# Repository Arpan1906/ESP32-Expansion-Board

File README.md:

# ESP32 Expansion Board

Designed by **Arpan Mukherjee**  
Date: 03/02/2026  

This repository contains the design files, schematics, and PCB layouts for an **ESP32 Expansion Board**. The board is built to simplify prototyping and interfacing with the ESP32-Devkit, providing organized pin headers, regulated power supply, and easy access to GPIOs.

---

## 📌 Features
- Compatible with **ESP32-Devkit V1**.
- Organized pin headers for:
  - Power: 3V3, 5V, VIN, GND
  - Digital I/O: D1 – D39
  - UART: RX0/TX0, RX2/TX2
  - Special pins: EN, VP, VN
- On-board **7805T voltage regulator** for +12V input → +5V output.
- Decoupling capacitors (C1, C2) for stable power.
- Jumper headers (JP1 – JP4) for flexible interfacing.
- Clear silkscreen labels for easy identification.
- Compact and symmetrical PCB layout for neat prototyping.

---

## Schematic

## Top Layer

## Bottom Layer

## Top Layer (Prior to Fabrication)

## Bottom Layer (Prior to Fabrication)

## 📂 Repository Contents
- **TOP.pdf** → Top layer PCB layout  
- **Bottom.pdf** → Bottom layer PCB layout  
- **Schematics** → ESP32 Expansion Board circuit diagram  
- **PCB Images** → Rendered PCB layouts for visualization  

---

## ⚡ Hardware Overview

### Power Section
- Input: +12V DC  
- Regulator: 7805T → +5V output  
- Outputs: +5V, 3V3, GND available on headers  

### Pin Mapping
| Left Header | Right Header | Center Header |
|-------------|--------------|---------------|
| 3V3, GND, D15, D2, D4, D5, D18, D19, D21, RX0, TX0, D22, D23 | +5V, GND, D13, D12, D14, D27, D26, D25, D33, D32, D35, D34, VN/D39, VP/D36, EN | IO15, IO2, IO4, IO16, IO17, IO5, IO18, IO19, IO21, IO3, IO1, IO22, IO23 |

---

## 🔧 How to Use
1. Connect **ESP32-Devkit V1** to the expansion board.  
2. Provide **+12V input** to the power terminal.  
3. Use headers to interface sensors, modules, or external circuits.  
4. Configure jumpers (JP1–JP4) as needed for custom connections.  

---

## 📸 Visuals
PCB layouts and schematics are included in this repository (`TOP.pdf`, `Bottom.pdf`, and schematic diagrams).  

---

## 📺 Additional Resources
- YouTube Channel: [The ElectroPath](https://www.youtube.com/@The_ElectroPath)  

---

## 📜 License
This project is released under the **MIT License**. You are free to use, modify, and distribute with attribution.

---

## 🙌 Acknowledgments
- Designed and developed by **Arpan Mukherjee (ECE)**

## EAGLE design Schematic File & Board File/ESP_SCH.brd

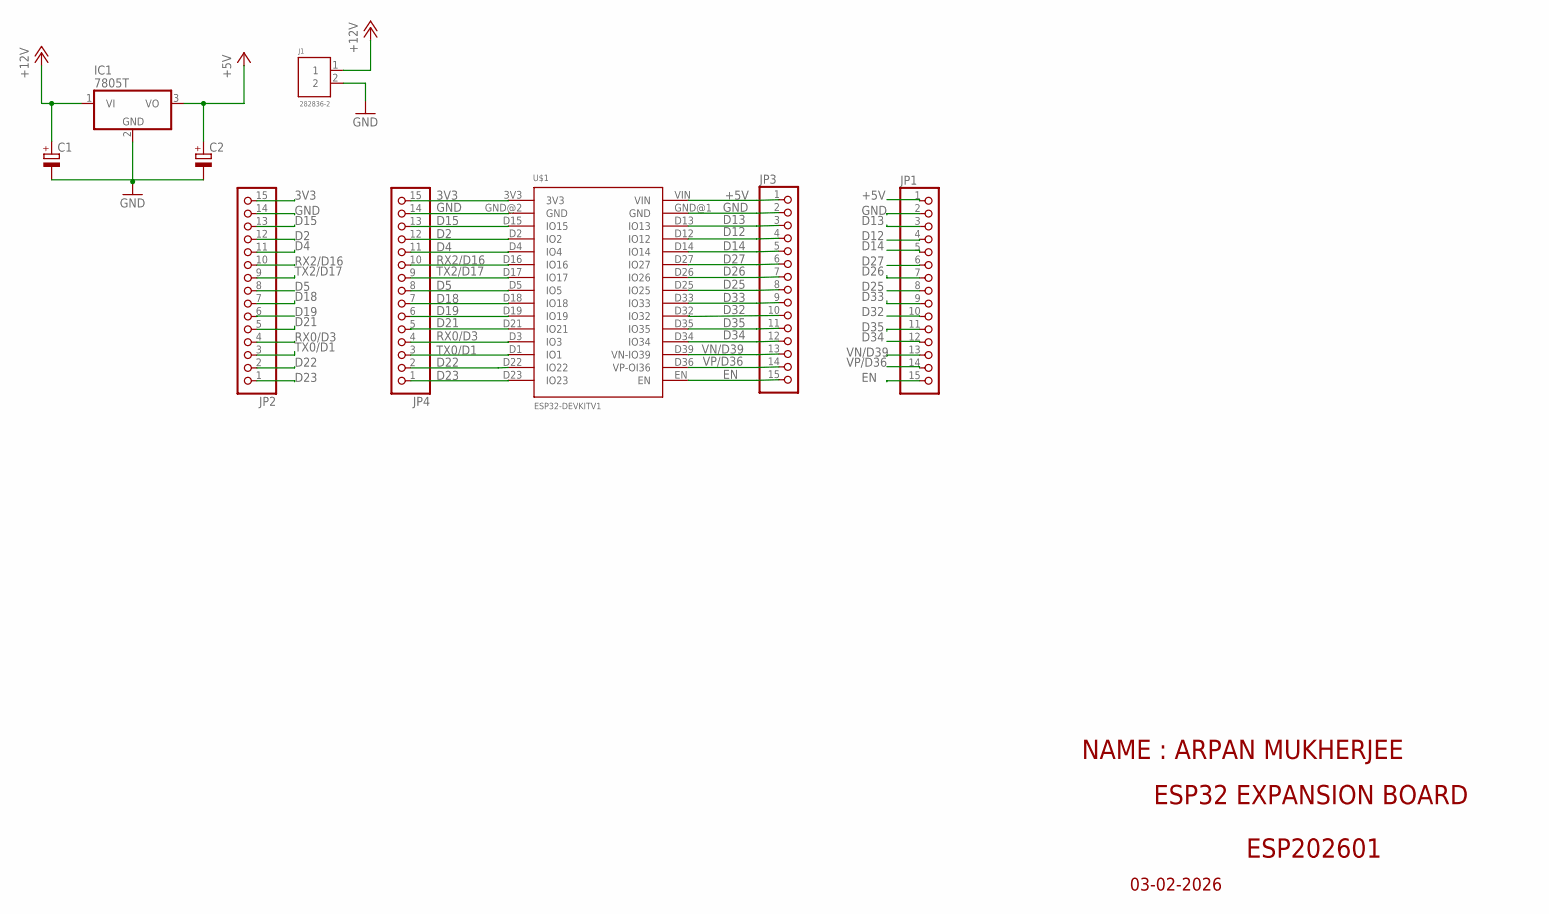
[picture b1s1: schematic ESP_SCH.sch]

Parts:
C1, C2: CPOL-EUE2.5-5; E2,5-5
IC1: 7805T; TO220H
J1: 282836-2; CONN_282836-2
JP1, JP2, JP3, JP4: PINHD-1X15; 1X15
U$1: ESP32DEVKITV1; ESP32-DEVKITV1

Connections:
3V3: JP2.15, JP4.15, U$1.3V3
+5V: C2.+, IC1.3 (VO), JP1.1, JP3.1, U$1.VIN
+12V: C1.+, IC1.1 (VI), J1.1
D2: JP2.12, JP4.12, U$1.D2 (IO2)
D4: JP2.11, JP4.11, U$1.D4 (IO4)
D5: JP2.8, JP4.8, U$1.D5 (IO5)
D12: JP1.4, JP3.4, U$1.D12 (IO12)
D13: JP1.3, JP3.3, U$1.D13 (IO13)
D14: JP1.5, JP3.5, U$1.D14 (IO14)
D15: JP2.13, JP4.13, U$1.D15 (IO15)
D18: JP2.7, JP4.7, U$1.D18 (IO18)
D19: JP2.6, JP4.6, U$1.D19 (IO19)
D21: JP2.5, JP4.5, U$1.D21 (IO21)
D22: JP2.2, JP4.2, U$1.D22 (IO22)
D23: JP2.1, JP4.1, U$1.D23 (IO23)
D25: JP1.8, JP3.8, U$1.D25 (IO25)
D26: JP1.7, JP3.7, U$1.D26 (IO26)
D27: JP1.6, JP3.6, U$1.D27 (IO27)
D32: JP1.10, JP3.10, U$1.D32 (IO32)
D33: JP1.9, JP3.9, U$1.D33 (IO33)
D34: JP1.12, JP3.12, U$1.D34 (IO34)
D35: JP1.11, JP3.11, U$1.D35 (IO35)
EN: JP1.15, JP3.15, U$1.EN
GND: C1.-, C2.-, IC1.2 (GND), J1.2, JP1.2, JP2.14, JP3.2, JP4.14, U$1.GND@1 (GND), U$1.GND@2 (GND)
RX0/D3: JP2.4, JP4.4, U$1.D3 (IO3)
RX2/D16: JP2.10, JP4.10, U$1.D16 (IO16)
TX0/D1: JP2.3, JP4.3, U$1.D1 (IO1)
TX2/D17: JP2.9, JP4.9, U$1.D17 (IO17)
VN/D39: JP1.13, JP3.13, U$1.D39 (VN-IO39)
VP/D36: JP1.14, JP3.14, U$1.D36 (VP-OI36)

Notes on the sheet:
NAME : ARPAN MUKHERJEE
ESP202601
03-02-2026
ESP32 EXPANSION BOARD

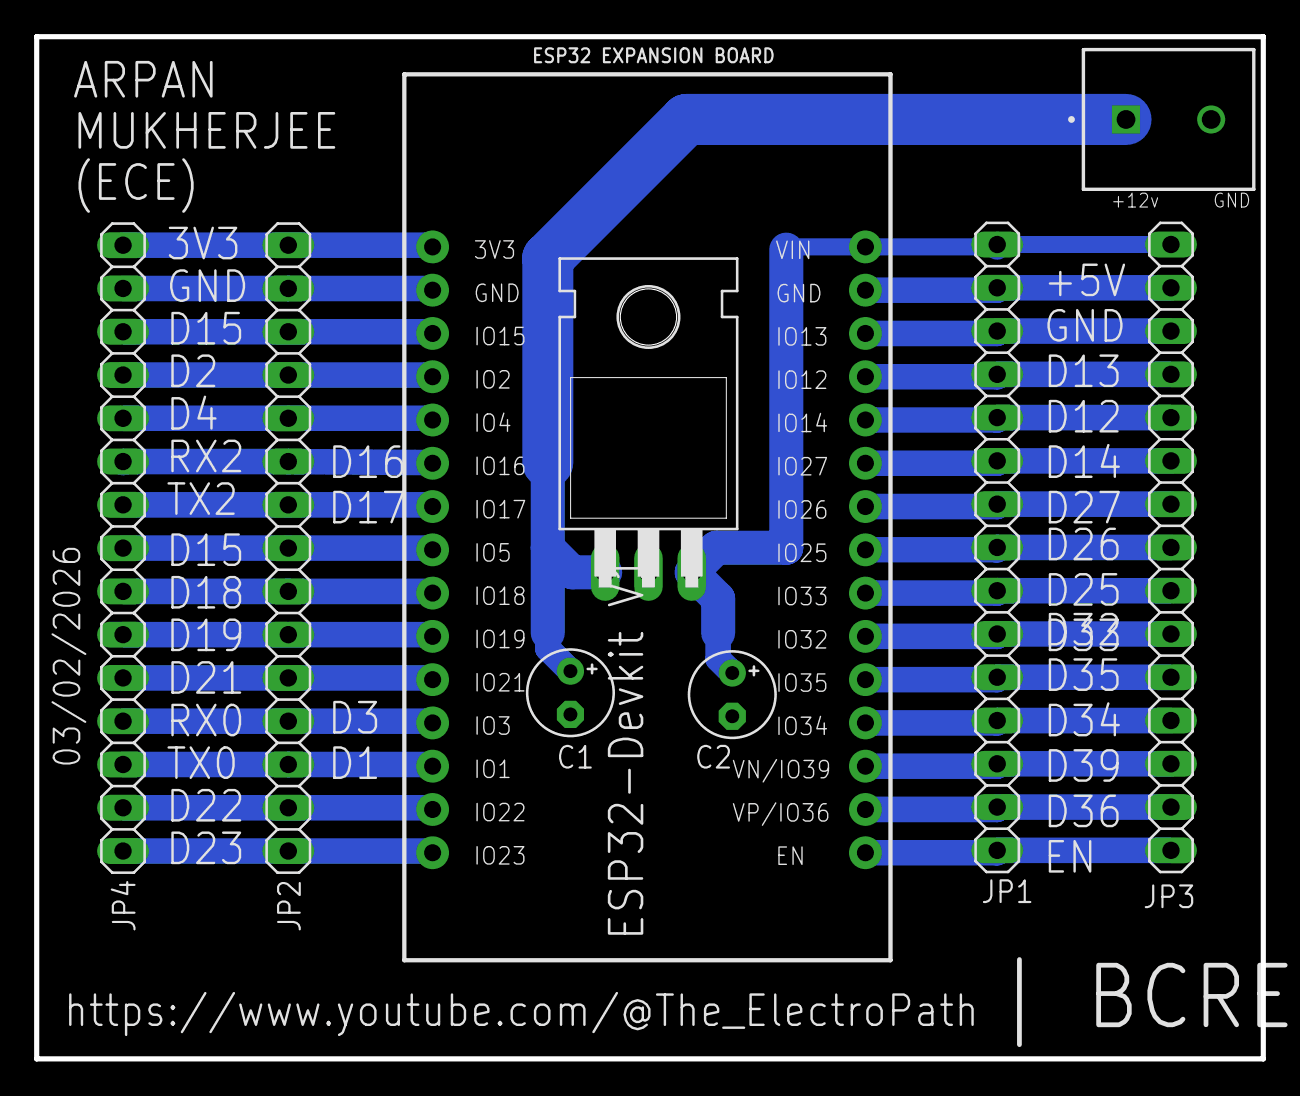
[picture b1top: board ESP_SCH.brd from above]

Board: 2 copper layers, 72.0 x 60.0 mm, 9 parts (0 on the bottom side), 30 nets.

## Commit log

2026-02-03 Enhance README with features and usage details
    Expanded README with detailed features, usage instructions, and visuals.
2026-02-03 Simplify README by removing initial details
    Removed introductory description and features list.
2026-02-03 Add Bottom Layer image to README
2026-02-03 Create Schematic File & Board File
2026-02-03 Create A
2026-02-03 Create b
2026-02-03 Create c
